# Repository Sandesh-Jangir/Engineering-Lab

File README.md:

# 🛠️ Engineering Lab

> A practical engineering workspace containing projects, experiments, simulations, implementations, and technical documentation.

This repository serves as a hands-on engineering archive where concepts are transformed into practical implementations through coding, simulation, hardware experimentation, and detailed documentation.

Alongside project work, this repository also contains technical notes, observations, and implementation learnings developed throughout the engineering process.

---

# 🎯 Purpose

The objective of this repository is to bridge the gap between theoretical understanding and practical engineering.

It is used to:

- Build and document engineering projects
- Experiment with technical concepts
- Create simulations and prototypes
- Maintain implementation notes
- Record engineering decisions and observations
- Develop practical problem-solving skills

---

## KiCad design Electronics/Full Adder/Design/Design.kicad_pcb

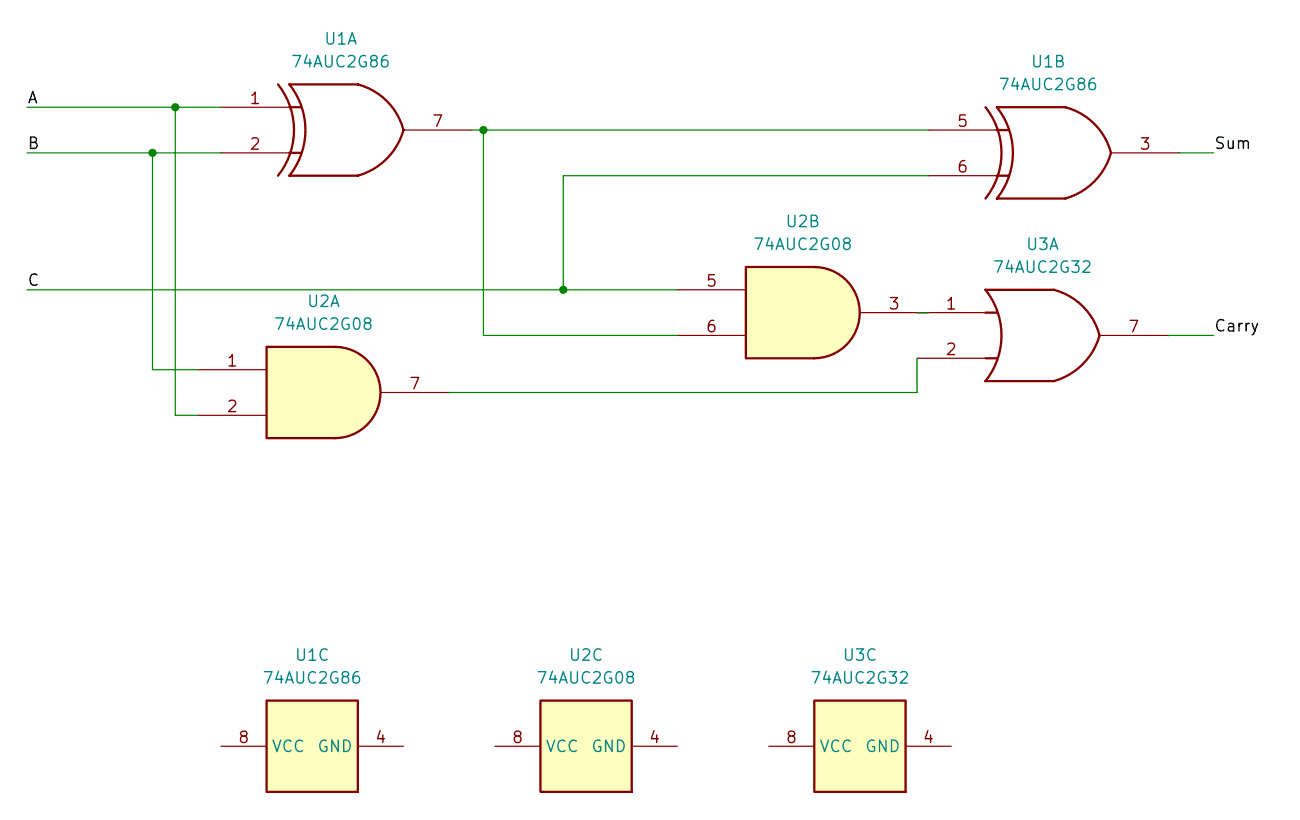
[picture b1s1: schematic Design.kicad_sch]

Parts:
U1: 74AUC2G86; SSOP-8_3.95x5.21x3.27mm_P1.27mm
U2: 74AUC2G08; SSOP-8_3.95x5.21x3.27mm_P1.27mm
U3: 74AUC2G32; SSOP-8_3.95x5.21x3.27mm_P1.27mm

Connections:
/A: U1.1, U2.2
/B: U1.2, U2.1
/C: U1.6, U2.5
/Carry: U3.7
/Sum: U1.3
unnamed: U1.5, U1.7, U2.6
unnamed: U2.3, U3.1
unnamed: U2.7, U3.2

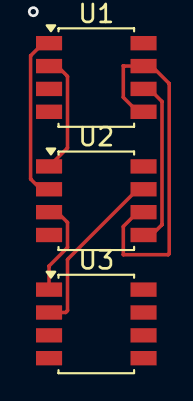
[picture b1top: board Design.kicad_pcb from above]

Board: 2 copper layers, 3 parts (0 on the bottom side), 6 nets.

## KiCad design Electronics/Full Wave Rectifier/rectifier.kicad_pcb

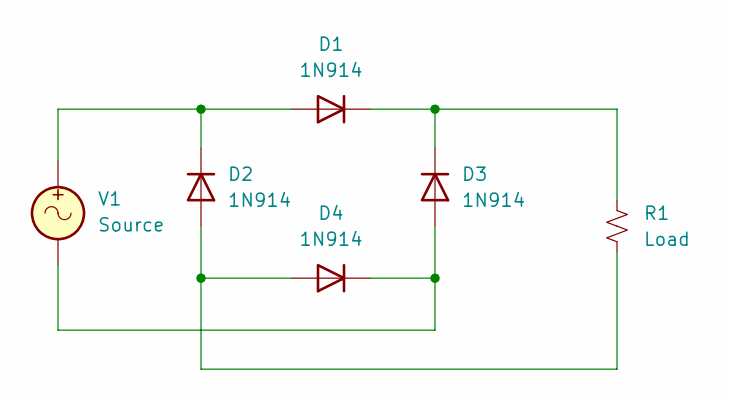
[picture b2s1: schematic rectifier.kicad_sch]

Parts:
D1, D2, D3, D4: 1N914; D_DO-35_SOD27_P7.62mm_Horizontal
R1: Load; R_01005_0402Metric_Pad0.57x0.30mm_HandSolder
V1: Source; R_0402_1005Metric

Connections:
unnamed: D1.2 (A), D2.1 (K), V1.1
unnamed: D1.1 (K), D3.1 (K), R1.1
unnamed: D2.2 (A), D4.2 (A), R1.2
unnamed: D3.2 (A), D4.1 (K), V1.2

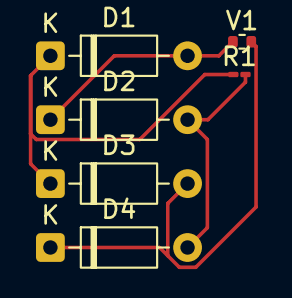
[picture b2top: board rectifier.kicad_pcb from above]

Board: 2 copper layers, 6 parts (0 on the bottom side), 4 nets.

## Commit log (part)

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2026-06-17 Submitted the task of operators and string.
2026-06-17 Add README.md for Engineering Lab overview
    This README provides an overview of the engineering lab repository, outlining its purpose and objectives.
2026-06-18 Completed strings and got started with arrays.
2026-06-18 modified the folder structure.
2026-06-18 Started CS50x Learnings.
2026-06-19 Completed the lessons with variable scopes, functions and array manipulations.
2026-06-20 Got done with conditionals in javascript.
2026-06-21 concluded fundamental javascript course.
2026-06-22 modified the folder sturcture.
2026-06-22 submitted js codebase for challenge - 01
2026-06-25 Designed and created my first arduino project.
2026-06-25 Craeted my first verilog circuit
2026-06-27 created schematics for traffic light programme, and added gitignores for unnecessary content.
2026-06-27 deleted the controvesial .history/
2026-06-27 completed the arduino progrmme.
2026-06-27 started tracking my leetcode progress as well.
2026-06-27 fixed a pylance issue.
2026-06-27 updated HDLBits problemset solutions.
2026-06-28 updated the learnings of basic verilog from hdlbits.
2026-06-28 updated leetcode problem.
